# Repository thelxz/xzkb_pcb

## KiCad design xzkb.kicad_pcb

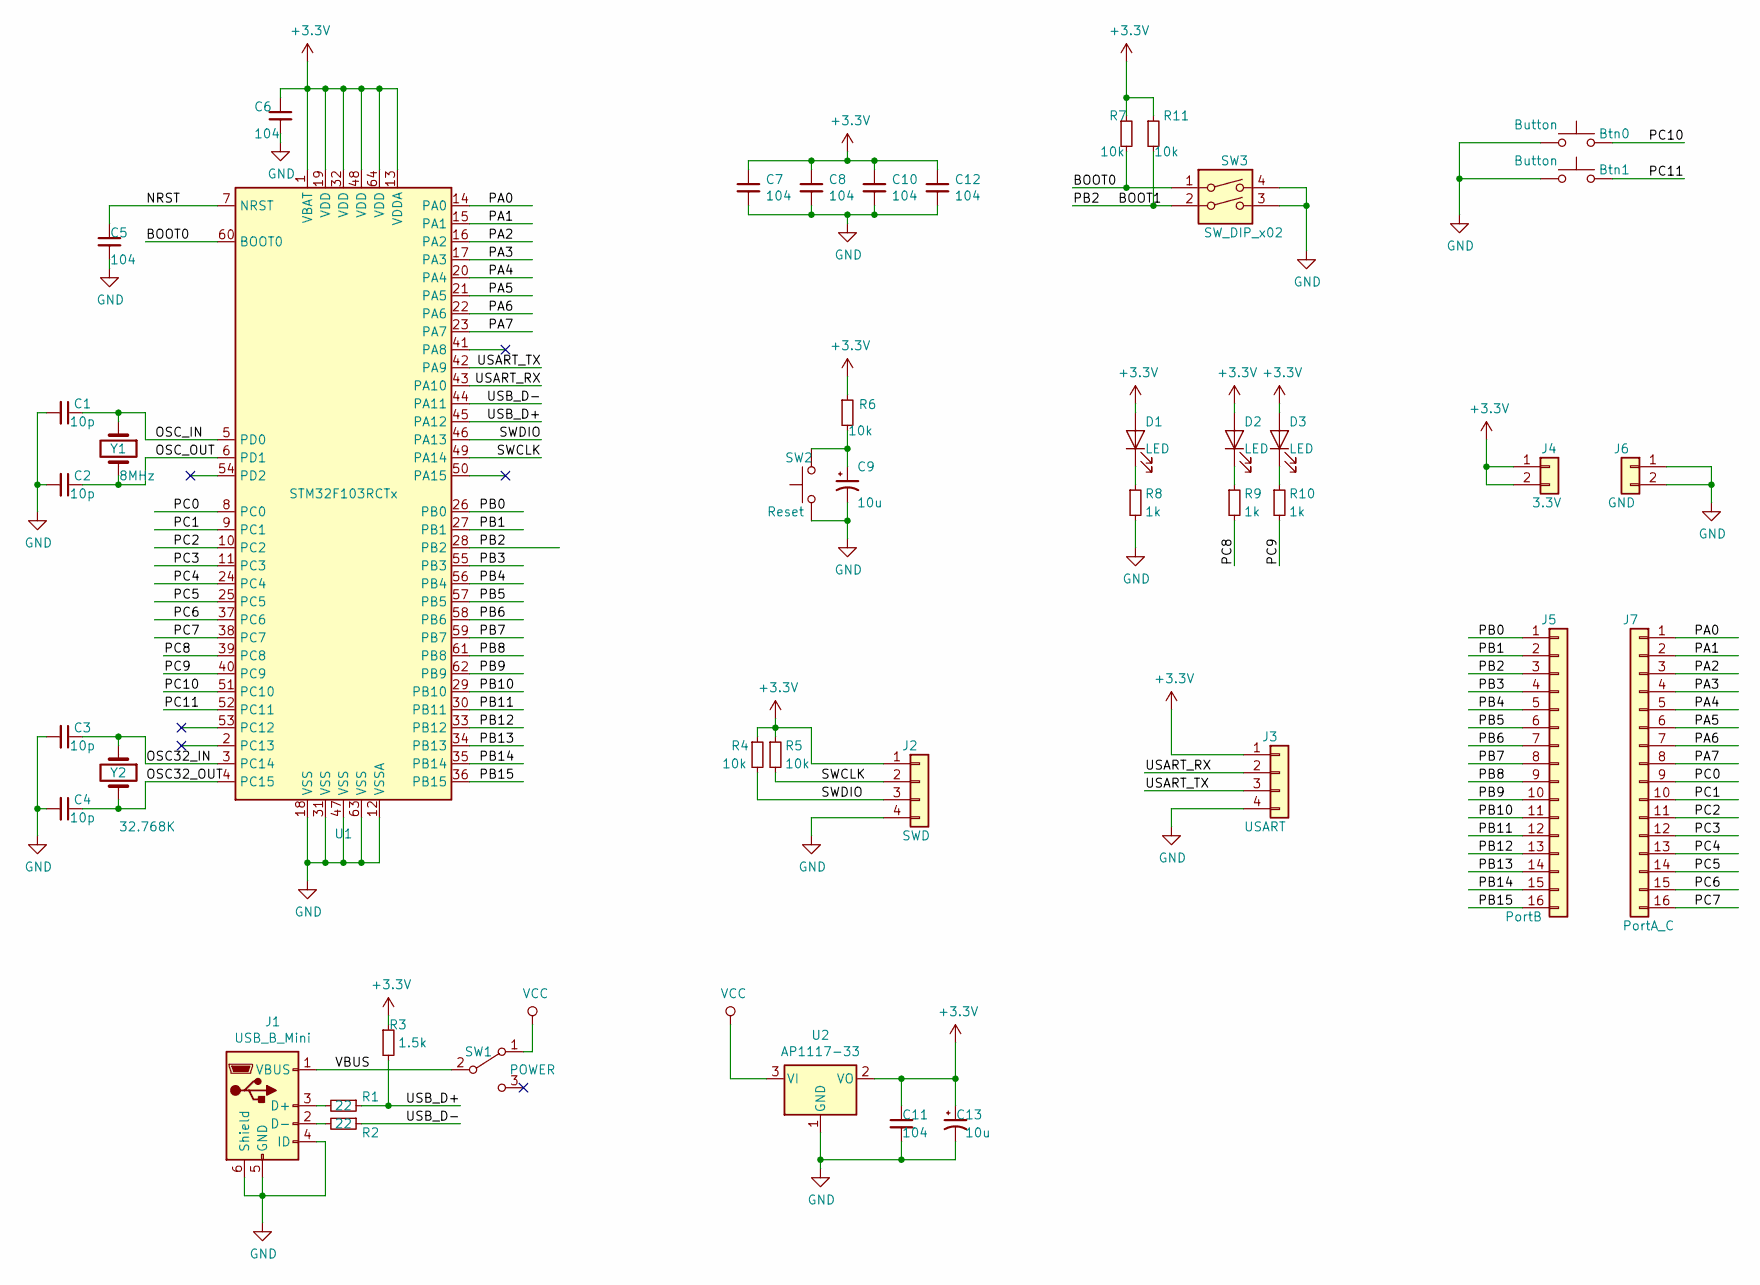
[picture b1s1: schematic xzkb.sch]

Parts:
Btn0, Btn1: Button; button_9.78x4.72mm_W8.61mm_P2.54mm
C1, C2, C3, C4: 10p; C_0805_2012Metric
C5, C6, C7, C8, C10, C11, C12: 104; C_0805_2012Metric
C9, C13: 10u; C_0805_2012Metric
D1, D2, D3: LED; LED_0805_2012Metric
J1: USB_B_Mini; USB_Mini-B_Lumberg_2486_01_Horizontal
J2: SWD; PinHeader_1x04_P2.54mm_Horizontal
J3: USART; PinHeader_1x04_P2.54mm_Vertical
J4: 3.3V; PinHeader_1x02_P2.54mm_Vertical
J5: PortB; PinHeader_1x16_P2.54mm_Vertical
J6: GND; PinHeader_1x02_P2.54mm_Vertical
J7: PortA_C; PinHeader_1x16_P2.54mm_Vertical
R1, R2: 22; R_0805_2012Metric
R3: 1.5k; R_0805_2012Metric
R4, R5, R6, R7, R11: 10k; R_0805_2012Metric
R8, R9, R10: 1k; R_0805_2012Metric
SW1: POWER; Switch_3Pin_P2.54mm_Vertical
SW2: Reset; SW_SPST_CK_RS282G05A3
SW3: SW_DIP_x02; SW_DIP_SPSTx02_Slide_Copal_CHS-02B_W7.62mm_P1.27mm
U1: STM32F103RCTx; LQFP-64_10x10mm_P0.5mm
U2: AP1117-33; SOT-223-3_TabPin2
Y1: 8MHz; Crystal_HC49-4H_Vertical
Y2: 32.768K; Crystal_C38-LF_D3.0mm_L8.0mm_Horizontal

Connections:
+3V3: C6.1, C7.1, C8.1, C10.1, C11.1, C12.1, C13.1, D1.2 (A), D2.2 (A), D3.2 (A), J2.1, J3.1, J4.1, J4.2, R3.1, R4.1, R5.1, R6.1, R7.1, R11.1, U1.1 (VBAT), U1.13 (VDDA), U1.19 (VDD), U1.32 (VDD), U1.48 (VDD), U1.64 (VDD), U2.2 (VO)
/BOOT0: R7.2, SW3.1, U1.60 (BOOT0)
/BOOT1: J5.3, R11.2, SW3.2, U1.28 (PB2)
/NRST: C5.1, U1.7 (NRST)
/OSC32_IN: C3.1, U1.3 (PC14), Y2.1
/OSC32_OUT: C4.1, U1.4 (PC15), Y2.2
/OSC_IN: C1.1, U1.5 (PD0), Y1.1
/OSC_OUT: C2.1, U1.6 (PD1), Y1.2
/PA0: J7.1, U1.14 (PA0)
/PA1: J7.2, U1.15 (PA1)
/PA2: J7.3, U1.16 (PA2)
/PA3: J7.4, U1.17 (PA3)
/PA4: J7.5, U1.20 (PA4)
/PA5: J7.6, U1.21 (PA5)
/PA6: J7.7, U1.22 (PA6)
/PA7: J7.8, U1.23 (PA7)
/PB0: J5.1, U1.26 (PB0)
/PB1: J5.2, U1.27 (PB1)
/PB3: J5.4, U1.55 (PB3)
/PB4: J5.5, U1.56 (PB4)
/PB5: J5.6, U1.57 (PB5)
/PB6: J5.7, U1.58 (PB6)
/PB7: J5.8, U1.59 (PB7)
/PB8: J5.9, U1.61 (PB8)
/PB9: J5.10, U1.62 (PB9)
/PB10: J5.11, U1.29 (PB10)
/PB11: J5.12, U1.30 (PB11)
/PB12: J5.13, U1.33 (PB12)
/PB13: J5.14, U1.34 (PB13)
/PB14: J5.15, U1.35 (PB14)
/PB15: J5.16, U1.36 (PB15)
/PC0: J7.9, U1.8 (PC0)
/PC1: J7.10, U1.9 (PC1)
/PC2: J7.11, U1.10 (PC2)
/PC3: J7.12, U1.11 (PC3)
/PC4: J7.13, U1.24 (PC4)
/PC5: J7.14, U1.25 (PC5)
/PC6: J7.15, U1.37 (PC6)
/PC7: J7.16, U1.38 (PC7)
/PC8: R9.2, U1.39 (PC8)
/PC9: R10.2, U1.40 (PC9)
/PC10: Btn0.2, U1.51 (PC10)
/PC11: Btn1.2, U1.52 (PC11)
/SWCLK: J2.2, R5.2, U1.49 (PA14)
/SWDIO: J2.3, R4.2, U1.46 (PA13)
/USART_RX: J3.2, U1.43 (PA10)
/USART_TX: J3.3, U1.42 (PA9)
/USB_D+: R1.1, R3.2, U1.45 (PA12)
/USB_D-: R2.1, U1.44 (PA11)
/VBUS: J1.1 (VBUS), SW1.2 (B)
GND: Btn0.1, Btn1.1, C1.2, C2.2, C3.2, C4.2, C5.2, C6.2, C7.2, C8.2, C9.2, C10.2, C11.2, C12.2, C13.2, J1.4 (ID), J1.5 (GND), J1.6 (Shield), J2.4, J3.4, J6.1, J6.2, R8.2, SW2.1, SW3.3, SW3.4, U1.12 (VSSA), U1.18 (VSS), U1.31 (VSS), U1.47 (VSS), U1.63 (VSS), U2.1 (GND)
unnamed: C9.1, R6.2, SW2.2
unnamed: D1.1 (K), R8.1
unnamed: D2.1 (K), R9.1
unnamed: D3.1 (K), R10.1
unnamed: J1.2 (D-), R2.2
unnamed: J1.3 (D+), R1.2
VCC: SW1.1 (A), U2.3 (VI)

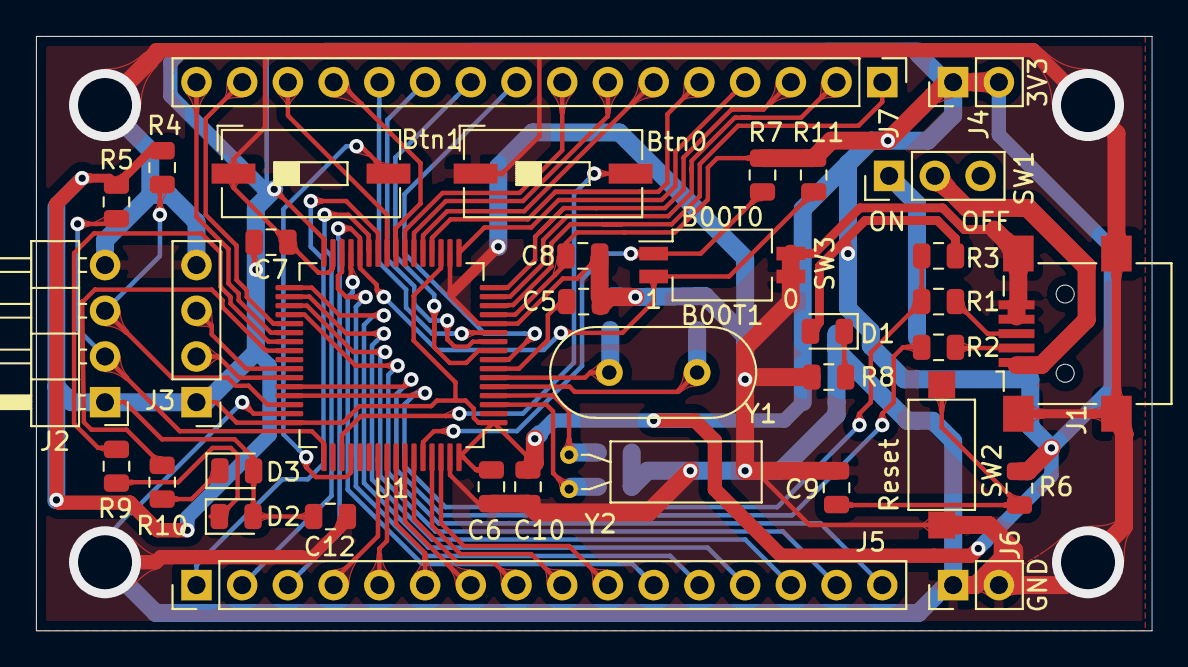
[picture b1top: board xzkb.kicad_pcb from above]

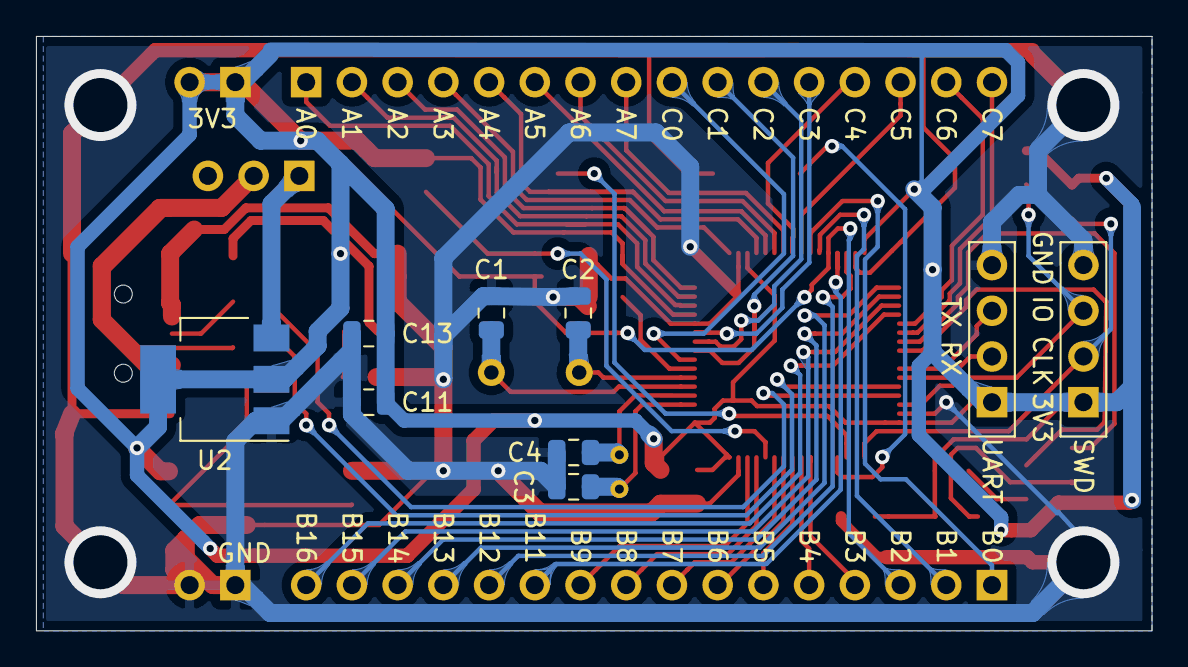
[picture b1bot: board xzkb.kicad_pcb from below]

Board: 2 copper layers, 62.0 x 33.0 mm, 43 parts (7 on the bottom side), 58 nets.

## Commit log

2020-05-10 first version of PCB
